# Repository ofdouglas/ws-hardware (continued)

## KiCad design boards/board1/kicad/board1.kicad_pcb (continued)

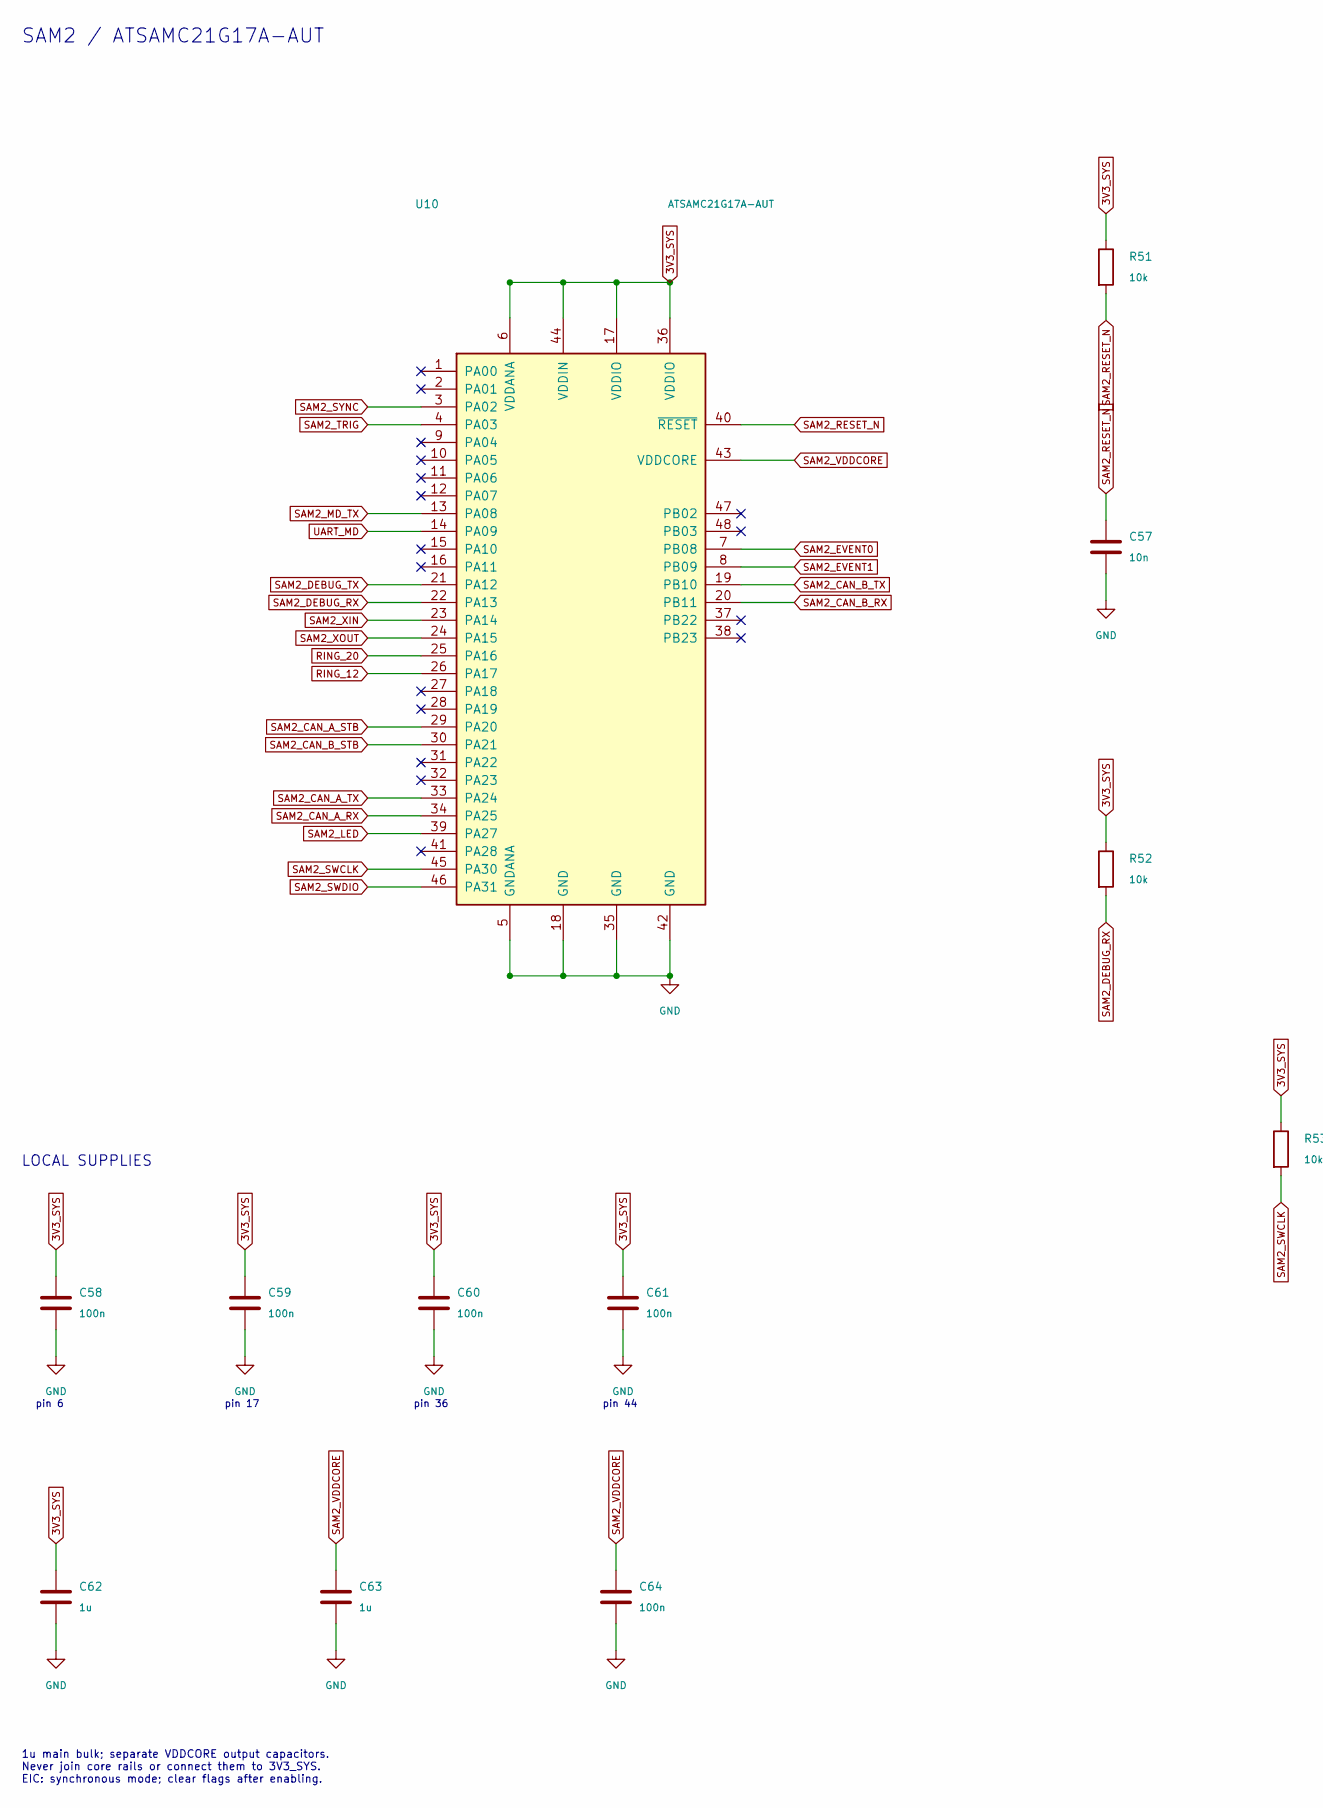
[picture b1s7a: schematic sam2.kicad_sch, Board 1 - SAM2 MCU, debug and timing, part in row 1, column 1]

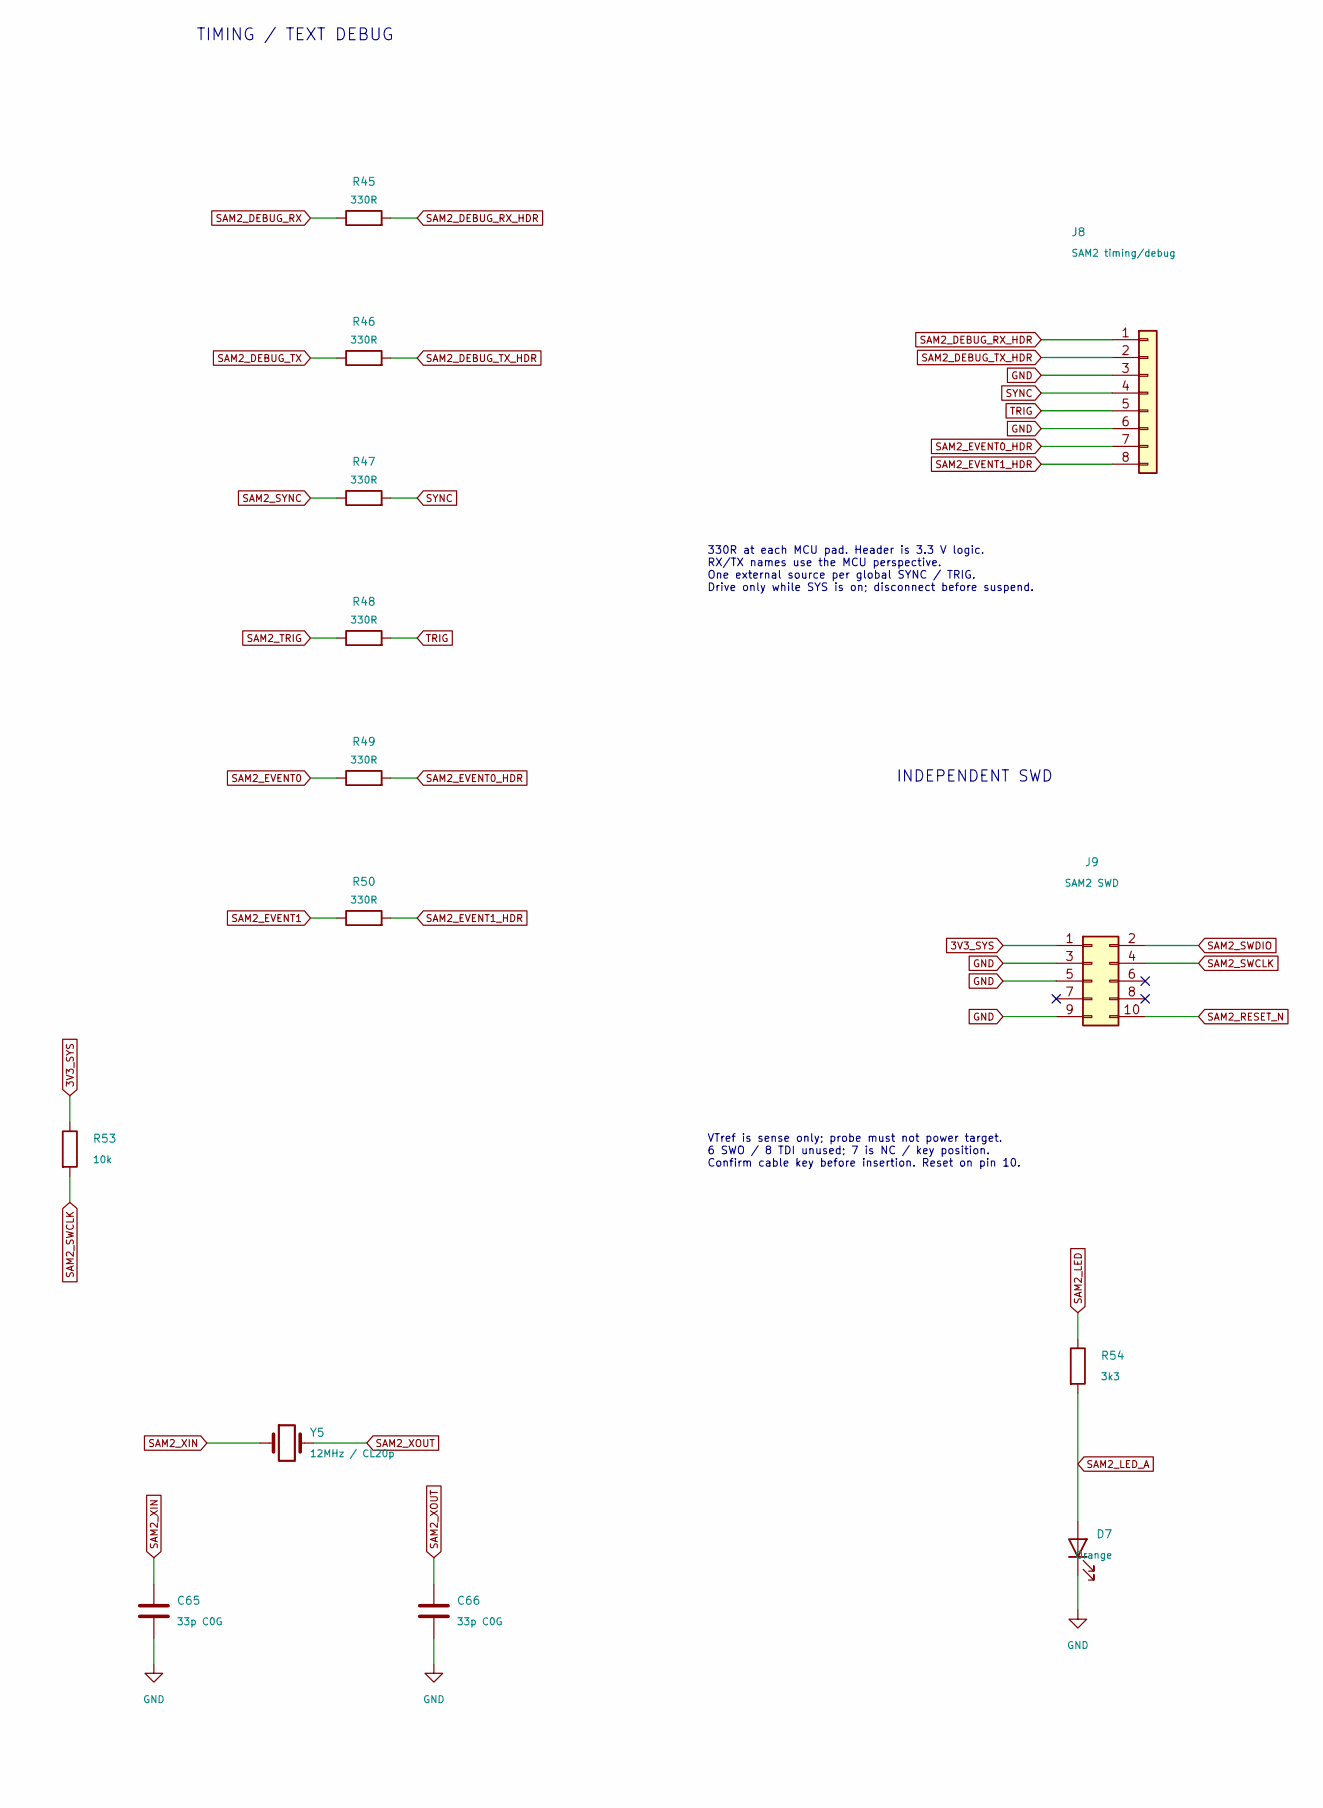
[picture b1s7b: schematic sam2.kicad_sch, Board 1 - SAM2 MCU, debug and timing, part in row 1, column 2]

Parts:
C57: 10n; C_0805_2012Metric; MPN CL21B103KBANNNC
C58, C59, C60, C61, C64: 100n; C_0805_2012Metric; MPN KGM21NR71E104KT
C62, C63: 1u; C_0805_2012Metric; MPN CL21B105KAFNFNE
C65, C66: 33p C0G; C_0805_2012Metric; MPN CC0805FRNPO9BN330
D7: Orange; LED_0603_1608Metric; MPN CSL1901DW1
J8: SAM2 timing/debug; PinHeader_1x08_P2.54mm_Vertical; MPN PRPC040SAAN-RC
J9: SAM2 SWD; CNC_Tech_3220-10-0100-00_2x05_P1.27mm_Vertical; MPN 3220-10-0100-00
R45, R46, R47, R48, R49, R50: 330R; R_0805_2012Metric; MPN CRGP0805F330R
R51, R52, R53: 10k; R_0805_2012Metric; MPN RMCF0805FT10K0
R54: 3k3; R_0805_2012Metric; MPN RK73H2ATTD3301F
U10: ATSAMC21G17A-AUT; TQFP-48_7x7mm_P0.5mm; MPN ATSAMC21G17A-AUT
Y5: 12MHz / CL20p; Crystal_SMD_ECS_CSM3X-2Pin_7.6x4.1mm; MPN ECS-120-20-3X-EN-TR

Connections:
3V3_SYS: C58.1, C59.1, C60.1, C61.1, C62.1, J9.1, R51.1, R52.1, R53.1, U10.6 (VDDANA), U10.17 (VDDIO), U10.36 (VDDIO), U10.44 (VDDIN); also elsewhere on the board
GND: C57.2, C58.2, C59.2, C60.2, C61.2, C62.2, C63.2, C64.2, C65.2, C66.2, D7.1 (K), J8.3, J8.6, J9.3, J9.5, J9.9, U10.5 (GNDANA), U10.18 (GND), U10.35 (GND), U10.42 (GND); also elsewhere on the board
RING_12: U10.26 (PA17); also elsewhere on the board
RING_20: U10.25 (PA16); also elsewhere on the board
SAM2_CAN_A_RX: U10.34 (PA25); also elsewhere on the board
SAM2_CAN_A_STB: U10.29 (PA20); also elsewhere on the board
SAM2_CAN_A_TX: U10.33 (PA24); also elsewhere on the board
SAM2_CAN_B_RX: U10.20 (PB11); also elsewhere on the board
SAM2_CAN_B_STB: U10.30 (PA21); also elsewhere on the board
SAM2_CAN_B_TX: U10.19 (PB10); also elsewhere on the board
SAM2_DEBUG_RX: R45.1, R52.2, U10.22 (PA13)
SAM2_DEBUG_RX_HDR: J8.1, R45.2
SAM2_DEBUG_TX: R46.1, U10.21 (PA12)
SAM2_DEBUG_TX_HDR: J8.2, R46.2
SAM2_EVENT0: R49.1, U10.7 (PB08)
SAM2_EVENT0_HDR: J8.7, R49.2
SAM2_EVENT1: R50.1, U10.8 (PB09)
SAM2_EVENT1_HDR: J8.8, R50.2
SAM2_LED: R54.1, U10.39 (PA27)
SAM2_LED_A: D7.2 (A), R54.2
SAM2_MD_TX: U10.13 (PA08); also elsewhere on the board
SAM2_RESET_N: C57.1, J9.10, R51.2, U10.40 (~RESET); also elsewhere on the board
SAM2_SWCLK: J9.4, R53.2, U10.45 (PA30)
SAM2_SWDIO: J9.2, U10.46 (PA31)
SAM2_SYNC: R47.1, U10.3 (PA02)
SAM2_TRIG: R48.1, U10.4 (PA03)
SAM2_VDDCORE: C63.1, C64.1, U10.43 (VDDCORE); also elsewhere on the board
SAM2_XIN: C65.1, U10.23 (PA14), Y5.1
SAM2_XOUT: C66.1, U10.24 (PA15), Y5.2
SYNC: J8.4, R47.2; also elsewhere on the board
TRIG: J8.5, R48.2; also elsewhere on the board
UART_MD: U10.14 (PA09); also elsewhere on the board

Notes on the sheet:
SAM2 / ATSAMC21G17A-AUT
TIMING / TEXT DEBUG
INDEPENDENT SWD
330R at each MCU pad. Header is 3.3 V logic. RX/TX names use the MCU perspective. One external source per global SYNC / TRIG. Drive only while SYS is on; disconnect before suspend.
VTref is sense only; probe must not power target. 6 SWO / 8 TDI unused; 7 is NC / key position. Confirm cable key before insertion. Reset on pin 10.
LOCAL SUPPLIES
pin 6
pin 17
pin 36
pin 44
1u main bulk; separate VDDCORE output capacitors. Never join core rails or connect them to 3V3_SYS. EIC: synchronous mode; clear flags after enabling.

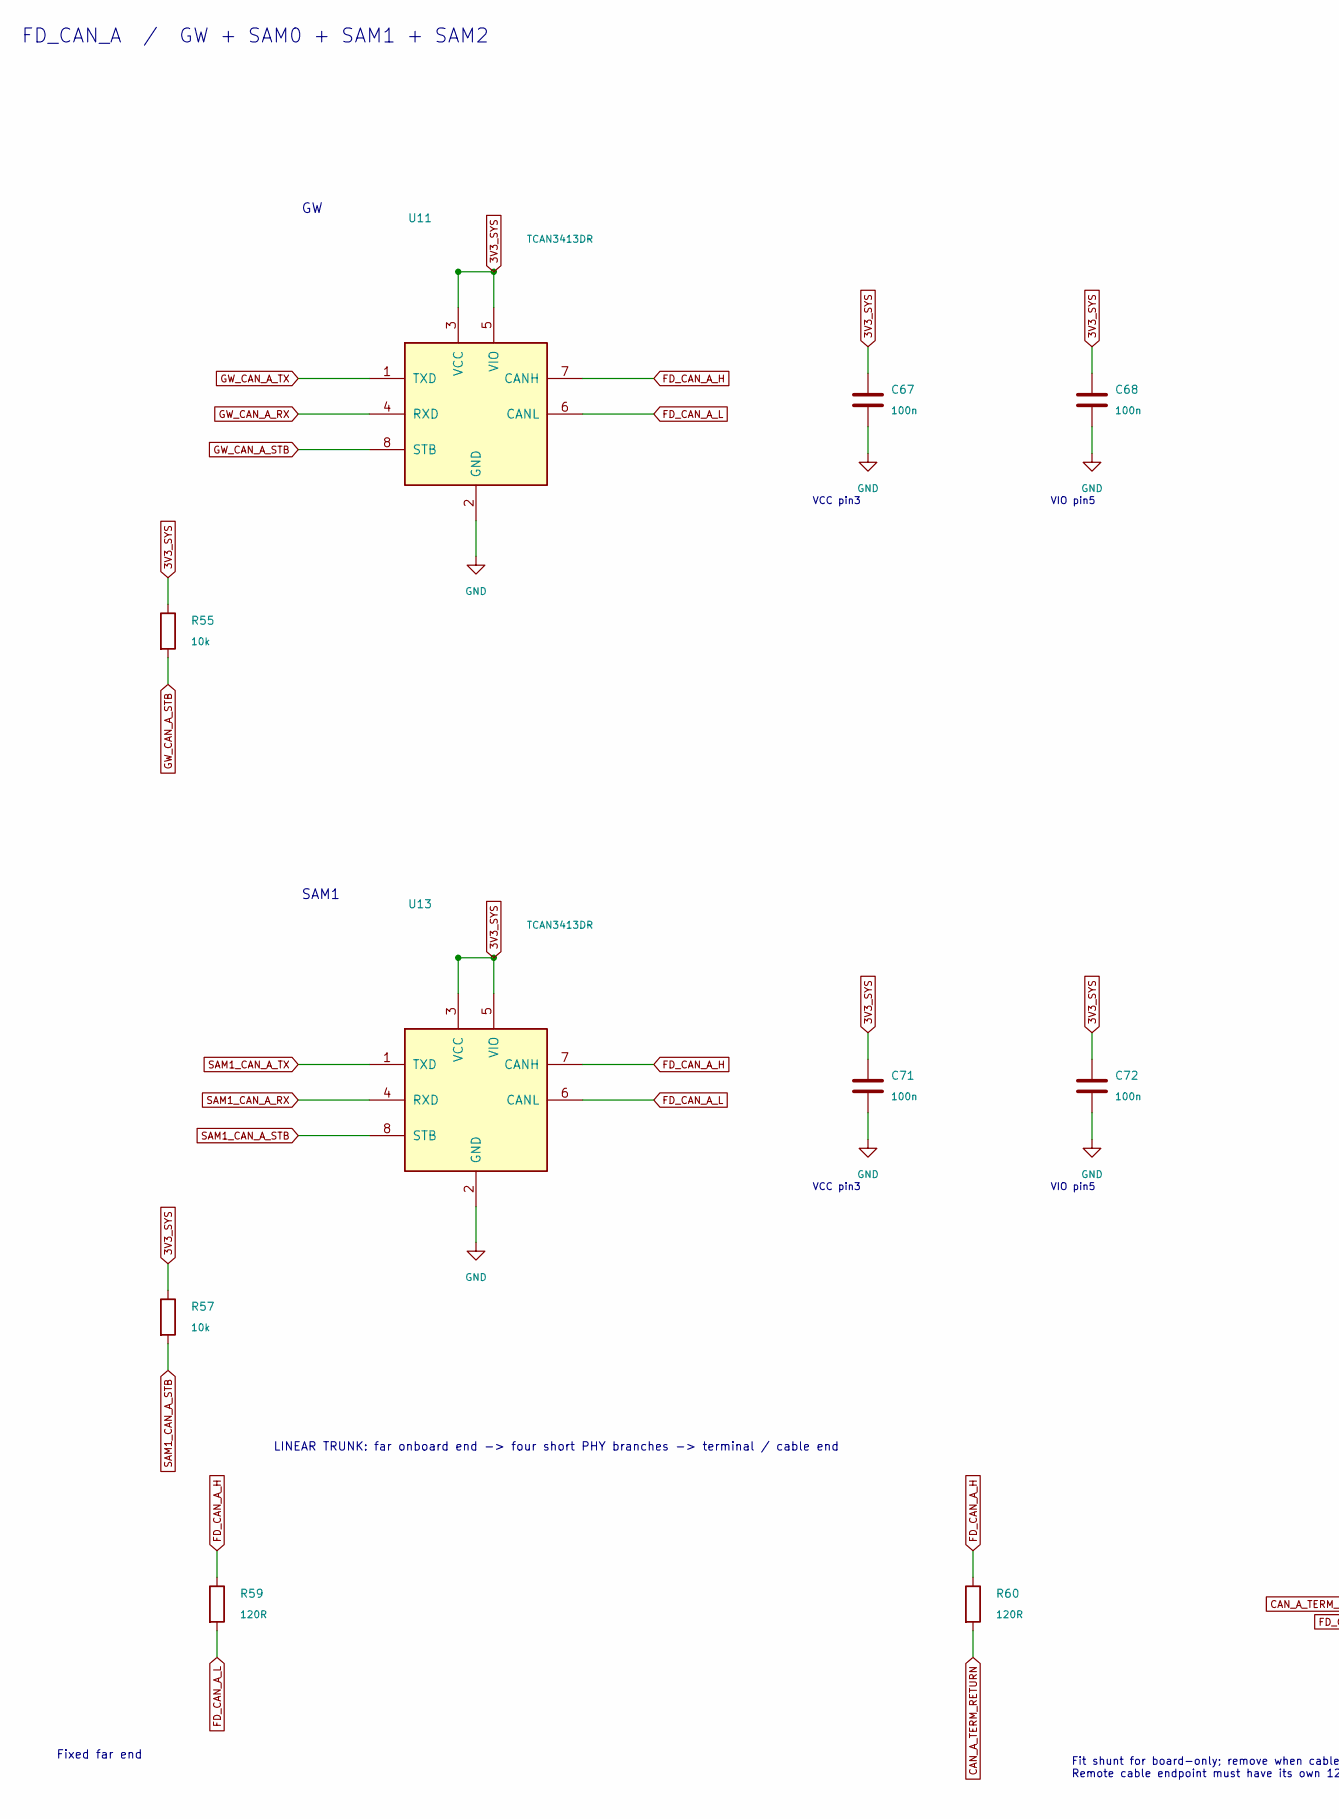
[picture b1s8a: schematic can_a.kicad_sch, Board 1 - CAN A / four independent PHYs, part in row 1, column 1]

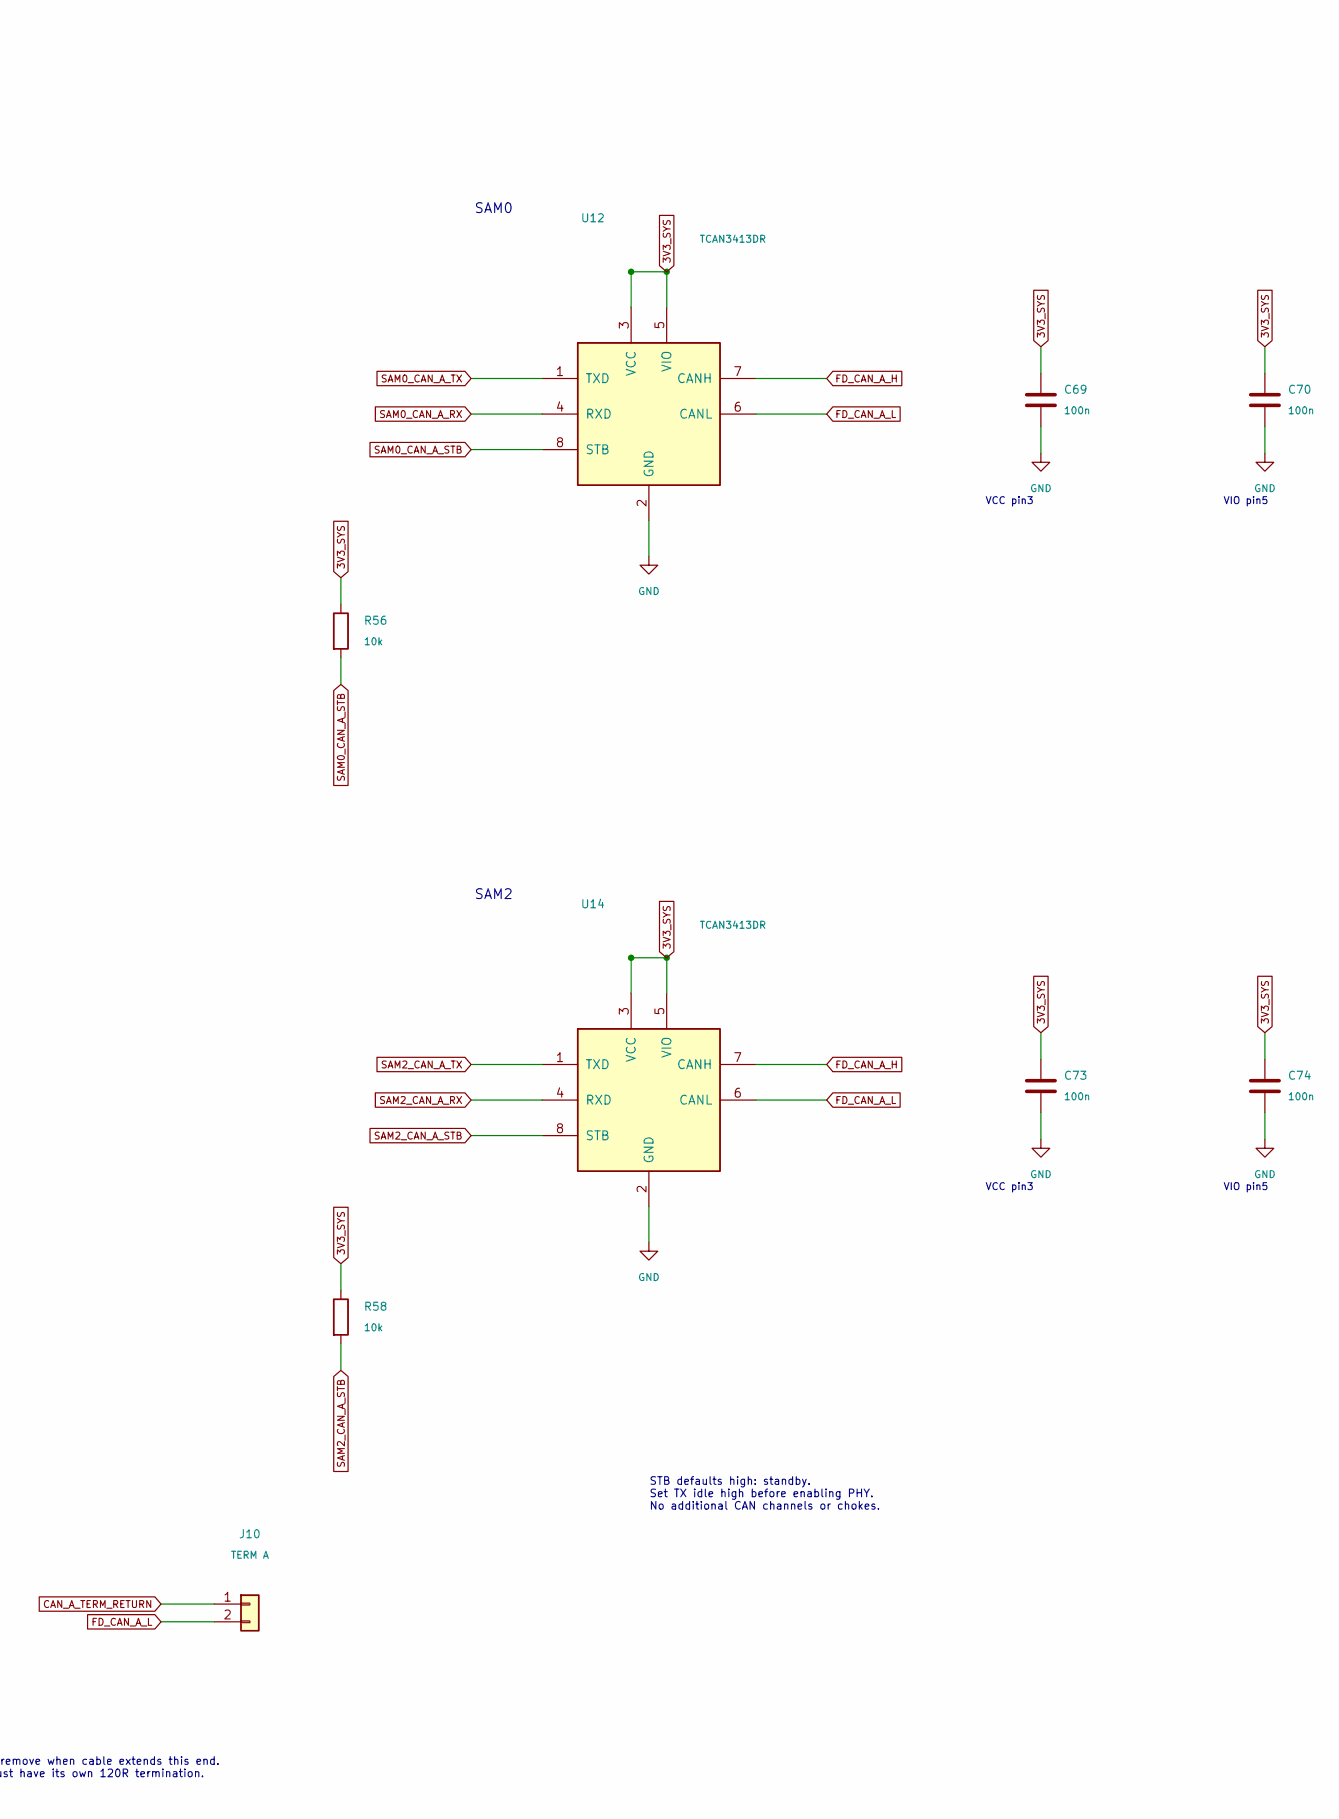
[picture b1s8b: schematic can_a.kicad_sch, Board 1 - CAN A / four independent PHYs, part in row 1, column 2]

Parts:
C67, C68, C69, C70, C71, C72, C73, C74: 100n; C_0805_2012Metric; MPN KGM21NR71E104KT
J10: TERM A; PinHeader_1x02_P2.54mm_Vertical; MPN PRPC002SAAN-RC
R55, R56, R57, R58: 10k; R_0805_2012Metric; MPN RMCF0805FT10K0
R59, R60: 120R; R_0805_2012Metric; MPN CRGP0805F120R
U11, U12, U13, U14: TCAN3413DR; SOIC-8_3.9x4.9mm_P1.27mm; MPN TCAN3413DR

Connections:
3V3_SYS: C67.1, C68.1, C69.1, C70.1, C71.1, C72.1, C73.1, C74.1, R55.1, R56.1, R57.1, R58.1, U11.3 (VCC), U11.5 (VIO), U12.3 (VCC), U12.5 (VIO), U13.3 (VCC), U13.5 (VIO), U14.3 (VCC), U14.5 (VIO); also elsewhere on the board
CAN_A_TERM_RETURN: J10.1, R60.2
FD_CAN_A_H: R59.1, R60.1, U11.7 (CANH), U12.7 (CANH), U13.7 (CANH), U14.7 (CANH); also elsewhere on the board
FD_CAN_A_L: J10.2, R59.2, U11.6 (CANL), U12.6 (CANL), U13.6 (CANL), U14.6 (CANL); also elsewhere on the board
GND: C67.2, C68.2, C69.2, C70.2, C71.2, C72.2, C73.2, C74.2, U11.2 (GND), U12.2 (GND), U13.2 (GND), U14.2 (GND); also elsewhere on the board
GW_CAN_A_RX: U11.4 (RXD); also elsewhere on the board
GW_CAN_A_STB: R55.2, U11.8 (STB); also elsewhere on the board
GW_CAN_A_TX: U11.1 (TXD); also elsewhere on the board
SAM0_CAN_A_RX: U12.4 (RXD); also elsewhere on the board
SAM0_CAN_A_STB: R56.2, U12.8 (STB); also elsewhere on the board
SAM0_CAN_A_TX: U12.1 (TXD); also elsewhere on the board
SAM1_CAN_A_RX: U13.4 (RXD); also elsewhere on the board
SAM1_CAN_A_STB: R57.2, U13.8 (STB); also elsewhere on the board
SAM1_CAN_A_TX: U13.1 (TXD); also elsewhere on the board
SAM2_CAN_A_RX: U14.4 (RXD); also elsewhere on the board
SAM2_CAN_A_STB: R58.2, U14.8 (STB); also elsewhere on the board
SAM2_CAN_A_TX: U14.1 (TXD); also elsewhere on the board

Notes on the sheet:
FD_CAN_A / GW + SAM0 + SAM1 + SAM2
VCC pin3
VIO pin5
SAM0
SAM1
SAM2
LINEAR TRUNK: far onboard end -> four short PHY branches -> terminal / cable end
Fixed far end
Fit shunt for board-only; remove when cable extends this end. Remote cable endpoint must have its own 120R termination.
STB defaults high: standby. Set TX idle high before enabling PHY. No additional CAN channels or chokes.

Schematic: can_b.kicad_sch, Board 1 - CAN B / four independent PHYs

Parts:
C75, C76, C77, C78, C79, C80, C81, C82: 100n; C_0805_2012Metric; MPN KGM21NR71E104KT
J11: TERM B; PinHeader_1x02_P2.54mm_Vertical; MPN PRPC002SAAN-RC
R61, R62, R63, R64: 10k; R_0805_2012Metric; MPN RMCF0805FT10K0
R65, R66: 120R; R_0805_2012Metric; MPN CRGP0805F120R
U15, U16, U17, U18: TCAN3413DR; SOIC-8_3.9x4.9mm_P1.27mm; MPN TCAN3413DR

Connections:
3V3_SYS: C75.1, C76.1, C77.1, C78.1, C79.1, C80.1, C81.1, C82.1, R61.1, R62.1, R63.1, R64.1, U15.3 (VCC), U15.5 (VIO), U16.3 (VCC), U16.5 (VIO), U17.3 (VCC), U17.5 (VIO), U18.3 (VCC), U18.5 (VIO); also elsewhere on the board
CAN_B_TERM_RETURN: J11.1, R66.2
FD_CAN_B_H: R65.1, R66.1, U15.7 (CANH), U16.7 (CANH), U17.7 (CANH), U18.7 (CANH); also elsewhere on the board
FD_CAN_B_L: J11.2, R65.2, U15.6 (CANL), U16.6 (CANL), U17.6 (CANL), U18.6 (CANL); also elsewhere on the board
GND: C75.2, C76.2, C77.2, C78.2, C79.2, C80.2, C81.2, C82.2, U15.2 (GND), U16.2 (GND), U17.2 (GND), U18.2 (GND); also elsewhere on the board
GW_CAN_B_RX: U15.4 (RXD); also elsewhere on the board
GW_CAN_B_STB: R61.2, U15.8 (STB); also elsewhere on the board
GW_CAN_B_TX: U15.1 (TXD); also elsewhere on the board
SAM0_CAN_B_RX: U16.4 (RXD); also elsewhere on the board
SAM0_CAN_B_STB: R62.2, U16.8 (STB); also elsewhere on the board
SAM0_CAN_B_TX: U16.1 (TXD); also elsewhere on the board
SAM1_CAN_B_RX: U17.4 (RXD); also elsewhere on the board
SAM1_CAN_B_STB: R63.2, U17.8 (STB); also elsewhere on the board
SAM1_CAN_B_TX: U17.1 (TXD); also elsewhere on the board
SAM2_CAN_B_RX: U18.4 (RXD); also elsewhere on the board
SAM2_CAN_B_STB: R64.2, U18.8 (STB); also elsewhere on the board
SAM2_CAN_B_TX: U18.1 (TXD); also elsewhere on the board

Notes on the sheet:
FD_CAN_B / GW + SAM0 + SAM1 + SAM2
VCC pin3
VIO pin5
SAM0
SAM1
SAM2
LINEAR TRUNK: far onboard end -> four short PHY branches -> terminal / cable end
Fixed far end
Fit shunt for board-only; remove when cable extends this end. Remote cable endpoint must have its own 120R termination.
STB defaults high: standby. Set TX idle high before enabling PHY. No additional CAN channels or chokes.

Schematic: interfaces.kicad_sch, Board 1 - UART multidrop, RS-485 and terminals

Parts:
C83, C84: 100n; C_0805_2012Metric; MPN KGM21NR71E104KT
R67, R68, R69, R70, R72, R73, R74, R75, R76, R77: 10k; R_0805_2012Metric; MPN RMCF0805FT10K0
R71: 470R; R_0805_2012Metric; MPN RMCF0805FT470R
R78, R80: 330R; R_0805_2012Metric; MPN CRGP0805F330R
R79: 120R; R_0805_2012Metric; MPN CRGP0805F120R
U19: SN74LV125APWR; TSSOP-14_4.4x5mm_P0.65mm; MPN SN74LV125APWR
U20: ST3485EBDR; SOIC-8_3.9x4.9mm_P1.27mm; MPN ST3485EBDR

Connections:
3V3_SYS: C83.1, C84.1, R67.1, R68.1, R69.1, R70.1, R71.1, R75.1, R76.1, R77.1, R78.1, U19.14 (VCC), U20.8 (VCC); also elsewhere on the board
GND: C83.2, C84.2, R72.2, R73.2, R74.2, R80.2, U19.2 (1A), U19.5 (2A), U19.7 (GND), U19.9 (3A), U19.12 (4A), U20.5 (GND); also elsewhere on the board
GW_MD_TX: R67.2, U19.1 (~1OE); also elsewhere on the board
GW_RS485_DE: R74.1, U20.3 (DE); also elsewhere on the board
GW_RS485_RE_N: R75.2, U20.2 (~RE); also elsewhere on the board
GW_RS485_RX: R77.2, U20.1 (RO); also elsewhere on the board
GW_RS485_TX: R76.2, U20.4 (DI); also elsewhere on the board
RS485_A: R78.2, R79.1, U20.6 (A); also elsewhere on the board
RS485_B: R79.2, R80.1, U20.7 (B); also elsewhere on the board
SAM0_MD_TX: R68.2, U19.4 (~2OE); also elsewhere on the board
SAM1_MD_TX: R69.2, U19.10 (~3OE); also elsewhere on the board
SAM2_MD_TX: R70.2, U19.13 (~4OE); also elsewhere on the board
SYNC: R72.1; also elsewhere on the board
TRIG: R73.1; also elsewhere on the board
UART_MD: R71.2, U19.3 (1Y), U19.6 (2Y), U19.8 (3Y), U19.11 (4Y); also elsewhere on the board

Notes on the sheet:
ONBOARD OPEN-DRAIN UART
All four RX inputs observe UART_MD. TX high releases; TX low sinks. No active-high drivers. Rate depends on measured rise time; firmware arbitrates.
EXTERNAL RS-485
DE low / RE_N high: reset shutdown. Fixed local termination; remote end also needs 120R. Both wires within +/-5.5 V of board GND (ADR-038).
Manual bench: disable / disconnect the RS-485 peer before USB power-off or suspend; bias can feed SYS. No automatic isolation or bias switch fitted.
Terminal block and TVS are on the test-access sheet.

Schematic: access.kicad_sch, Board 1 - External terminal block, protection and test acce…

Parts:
D8, D9: ESD2CAN24DBZRQ1; SOT-23; MPN ESD2CAN24DBZRQ1
D10: ESDS452DBZR; SOT-23; MPN ESDS452DBZR
J12: 1989803 / bus terminals; PhoenixContact_PTSA_0.5_8-2.5-F_1989803; MPN 1989803
J13: GW GND; PinHeader_1x02_P2.54mm_Vertical; MPN PRPC002SAAN-RC
J14: SAM0 GND; PinHeader_1x02_P2.54mm_Vertical; MPN PRPC002SAAN-RC
J15: SAM1 GND; PinHeader_1x02_P2.54mm_Vertical; MPN PRPC002SAAN-RC
J16: SAM2 GND; PinHeader_1x02_P2.54mm_Vertical; MPN PRPC002SAAN-RC
J17: POWER GND; PinHeader_1x02_P2.54mm_Vertical; MPN PRPC002SAAN-RC
J18: BUS GND; PinHeader_1x02_P2.54mm_Vertical; MPN PRPC002SAAN-RC
J19: CAN A; PinHeader_1x02_P2.54mm_Vertical; MPN PRPC002SAAN-RC
J20: CAN B; PinHeader_1x02_P2.54mm_Vertical; MPN PRPC002SAAN-RC
J21: RS485; PinHeader_1x02_P2.54mm_Vertical; MPN PRPC002SAAN-RC
J22: RING01; PinHeader_1x02_P2.54mm_Vertical; MPN PRPC002SAAN-RC
J23: RING12; PinHeader_1x02_P2.54mm_Vertical; MPN PRPC002SAAN-RC
J24: RING20; PinHeader_1x02_P2.54mm_Vertical; MPN PRPC002SAAN-RC
J25: UART_MD; PinHeader_1x02_P2.54mm_Vertical; MPN PRPC002SAAN-RC
TP1: VBUS_RAW; TestPoint_Pad_D2.0mm; MPN NA
TP2: USB_5V; TestPoint_Pad_D2.0mm; MPN NA
TP3: FTDI_3V3; TestPoint_Pad_D2.0mm; MPN NA
TP4: 3V3_SYS; TestPoint_Pad_D2.0mm; MPN NA
TP5: GW_RESET_N; TestPoint_Pad_D2.0mm; MPN NA
TP6: GW_BOOT0; TestPoint_Pad_D2.0mm; MPN NA
TP7: SAM0_RESET_N; TestPoint_Pad_D2.0mm; MPN NA
TP8: SAM0_VDDCORE; TestPoint_Pad_D2.0mm; MPN NA
TP9: SAM1_RESET_N; TestPoint_Pad_D2.0mm; MPN NA
TP10: SAM1_VDDCORE; TestPoint_Pad_D2.0mm; MPN NA
TP11: SAM2_RESET_N; TestPoint_Pad_D2.0mm; MPN NA
TP12: SAM2_VDDCORE; TestPoint_Pad_D2.0mm; MPN NA

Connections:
3V3_SYS: TP4.1; also elsewhere on the board
FD_CAN_A_H: D8.1 (IO1), J12.1, J19.1; also elsewhere on the board
FD_CAN_A_L: D8.2 (IO2), J12.2, J19.2; also elsewhere on the board
FD_CAN_B_H: D9.1 (IO1), J12.4, J20.1; also elsewhere on the board
FD_CAN_B_L: D9.2 (IO2), J12.5, J20.2; also elsewhere on the board
FTDI_3V3: TP3.1; also elsewhere on the board
GND: D8.3 (GND), D9.3 (GND), D10.3 (GND), J12.3, J12.8, J13.1, J13.2, J14.1, J14.2, J15.1, J15.2, J16.1, J16.2, J17.1, J17.2, J18.1, J18.2, J22.2, J23.2, J24.2, J25.2; also elsewhere on the board
GW_BOOT0: TP6.1; also elsewhere on the board
GW_RESET_N: TP5.1; also elsewhere on the board
RING_01: J22.1; also elsewhere on the board
RING_12: J23.1; also elsewhere on the board
RING_20: J24.1; also elsewhere on the board
RS485_A: D10.1 (IO1), J12.6, J21.1; also elsewhere on the board
RS485_B: D10.2 (IO2), J12.7, J21.2; also elsewhere on the board
SAM0_RESET_N: TP7.1; also elsewhere on the board
SAM0_VDDCORE: TP8.1; also elsewhere on the board
SAM1_RESET_N: TP9.1; also elsewhere on the board
SAM1_VDDCORE: TP10.1; also elsewhere on the board
SAM2_RESET_N: TP11.1; also elsewhere on the board
SAM2_VDDCORE: TP12.1; also elsewhere on the board
UART_MD: J25.1; also elsewhere on the board
USB_5V: TP2.1; also elsewhere on the board
VBUS_RAW: TP1.1; also elsewhere on the board

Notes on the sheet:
EXTERNAL BUS TERMINALS
TVS channels stay connected when CAN termination shunts are removed. Place all three arrays at terminal entry.
FITTED SCOPE GROUND POSTS
Six dedicated 1x2 headers, both contacts grounded. Place near the named circuit with room for a scope clip.
PCB TEST PADS — power / reset / core rails (TP1–TP12)

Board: 2 copper layers, 243 parts (0 on the bottom side), 152 nets, no tracks yet.

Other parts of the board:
H1, H2, H3, H4: M3 NPTH; MountingHole_3.2mm_M3

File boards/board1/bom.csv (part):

item_id,references,quantity,function,manufacturer,mpn,package,value,assembly,selection_status,evidence_status,symbol,footprint,requirements,adr,datasheet_evidence,sourcing_evidence,notes
B1-B001,U7,1,Gateway MCU,STMicroelectronics,STM32G474RBT6,LQFP64 (source; verify),NA,fit,accepted,unverified,MCU_ST_STM32G4:STM32G474RBTx,Package_QFP:LQFP-64_10x10mm_P0.5mm,B1-R001,ADR-004,DS12288 Rev.6 Fig.7 p.50; Tables12/13 pp.57-75; draft STM32 sheet linked in pinmap.md; ES0430 Rev.9 implementation review pending B1-Q005,TBD,Selected USR-15 / ADR-004; exact-device implementation and sourcing verification pending
B1-B002,U8; U9; U10,3,Leaf MCU,Microchip,ATSAMC21G17A-AUT,TQFP48 (source; verify),NA,fit,accepted,unverified,ATSAMC21G17A-AUT:ATSAMC21G17A-AUT,Package_QFP:TQFP-48_7x7mm_P0.5mm,B1-R001,ADR-004,DS60001479J sec.4.2.1 p.22; Table 6-2 pp.29-30; draft spreadsheet linked from pinmap.md; errata/footprint/electrical qualification pending B1-Q005; ../../libraries/symbols/ATSAMC21G17A-AUT/README.md (symbol evidence only; allocation remains unverified),TBD,Selected USR-15 / ADR-004; exact-device implementation and sourcing verification pending
B1-B003,U11; U12; U13; U14; U15; U16; U17; U18,8,CAN-FD PHYs,Texas Instruments,TCAN3413DR,SOIC-8; footprint review pending,TBD,fit,accepted,unverified,TCAN3413DR:TCAN3413DR,Package_SO:SOIC-8_3.9x4.9mm_P1.27mm,B1-R002,ADR-002,usb_input.md; TI SLLSFS8A; ../../libraries/symbols/TCAN3413DR/README.md (symbol pin evidence; board allocation unverified),2026-09-06 TI active; distributor stock/price TBD,TCAN3413DR selected USR-06; eight Rev A; ninth only in expanded Board 1; implementation unverified
B1-B004,U4,1,USB-UART bridge,FTDI,FT232HL-REEL,LQFP48; footprint review pending,TBD,fit,accepted,unverified,Board1:FT232HL_BusPowered,Package_QFP:LQFP-48_7x7mm_P0.5mm,B1-R005,ADR-001,FT232H DS_FT232H v2.2 pp.6-10 and Fig.6.1 p.45; kicad/README.md; full current errata/inventory reconciliation pending,USR-03: FT232HL on hand; linked ordering code 768-1101-1-ND,Captured U4 with project-local bus-powered symbol correcting VCCD/EECLK/EECS electrical types; pin numbers unchanged. On hand per user; exact inventory suffix/silicon revision to reconcile. Workbook B1-P233-280 remains unverified; see pinmap.md for CAD naming mapping.
B1-B005,J1,1,USB 2.0 Standard-B receptacle,On Shore Technology Inc.,USB-B1HSB6,TBD,TBD,fit,accepted,unverified,Connector:USB_B,Connector_USB:USB_B_OST_USB-B1HSxx_Horizontal,B1-R005,ADR-001; ADR-030,TBD,DigiKey ED2983-ND; https://www.digikey.com/en/products/detail/on-shore-technolo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,"J1 pins 1 VBUS, 2 DM, 3 DP, 4 GND, 5 shell. Draft connects shell directly to ground at entry. KiCad OST USB-B1HSxx footprint selected; exact housing/drill/land-pattern approval before layout remains B1-Q004."
B1-B006,D1,1,VBUS TVS,Littelfuse,SMF6.0A,SOD-123F,TBD,fit,accepted,unverified,Device:D,Diode_SMD:D_SOD-123F,B1-R006,ADR-019; ADR-022; ADR-024,usb_input.md,TBD,ESD/hotplug only; not a guaranteed <=6 V clamp or polarity/OVP circuit Captured in KiCad power/USB section; see kicad/README.md. Evidence remains unverified pending schematic/footprint approval.
B1-B007,NA,0,Remaining CAN interface protection,TBD,TBD,TBD,TBD,tbd,proposed,unverified,TBD,TBD,B1-R009,ADR-002; ADR-034; ADR-037,termination.md; B1-Q003/004,TBD,Residual allocation fully enumerated in completed schematic; no unassigned components or DNP footprints. See complete capture notes.
B1-B008,R67; R68; R69; R70,4,UART_MD driver /OE pull-up resistors,Stackpole Electronics Inc.,RMCF0805FT10K0,0805,10 kohm +/-1%; 0.125 W,fit,accepted,unverified,Device:R,Resistor_SMD:R_0805_2012Metric,B1-R003,ADR-033; ADR-039,https://www.seielect.com/Catalog/SEI-RMCF_RMCP.pdf ; ADR-033; B1-Q003,RMCF0805FT10K0CT-ND; refresh before purchase,"USR-33 accepts multidrop plan. Four /OE pull-ups to 3V3_SYS, one per driver channel. Shared bus pull-up split to B1-B074; driver B1-B066 and bypass B1-B036 counted separately. Reset/ramp/timing and baud remain unverified."
B1-B009,J3; J5; J7; J9,4,Independent Cortex SWD/reset headers,CNC Tech,3220-10-0100-00,Through-hole; 2 x 5; 1.27 mm; shrouded keyed header; footprint TBD,10 positions,fit,accepted,unverified,Connector_Generic:Conn_02x05_Odd_Even,Board1:CNC_Tech_3220-10-0100-00_2x05_P1.27mm_Vertical,B1-R007,ADR-011; ADR-026 (026-reva-connectors.md),https://www.cnctech.us/pdfs/3220-XX-0100-00_.pdf ; p.1; revision and footprint review TBD B1-Q004,DigiKey 1175-1627-ND; https://www.digikey.com/en/products/detail/cnc-tech/3220-10-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 ; refresh stock/price before purchase,Exact MPN selected USR-25 / ADR-026; four independent MCU headers. All ten contacts supplied; review position-7 removal against actual cable. Adapter/probe support and USB-only target-power behavior pending B1-Q004/005. Manufacturer drawing matched to native footprint; see kicad/footprint_checks.md. Physical sample/mating checks remain before layout approval.
B1-B010,NA,0,Remaining MCU boot/reset support,TBD,TBD,TBD,TBD,tbd,proposed,unverified,TBD,TBD,B1-R001,ADR-004,TBD,TBD,Residual allocation fully enumerated in completed schematic; no unassigned components or DNP footprints. See complete capture notes.
B1-B011,TP1; TP2; TP3; TP4; TP5; TP6; TP7; TP8; TP9; TP10; TP11; TP12; TP13; TP14; TP15; TP16; TP17; TP18; TP19,0,PCB test pads; no purchased components,NA,NA,PCB copper pads,2 mm exposed copper test pad; 19 placements,tbd,accepted,unverified,Connector:TestPoint,TestPoint:TestPoint_Pad_D2.0mm,B1-R008,ADR-039,TBD,TBD,"Nineteen pads, zero purchased parts. Named signals in schematic. Layout must keep high-speed observation branches short."
B1-B012,U2,1,3.3 V buck regulator,Texas Instruments,TPS560430X3FDBVR,SOT-23-6,3.3 V fixed; 600 mA; 1.1 MHz FPWM,fit,accepted,unverified,TPS560430X3FDBVR:TPS560430X3FDBVR,Package_TO_SOT_SMD:SOT-23-6,B1-R006; B1-R012; B1-R023,ADR-021,https://www.ti.com/lit/ds/symlink/tps560430.pdf; ../../libraries/symbols/TPS560430X3FDBVR/README.md (symbol pin evidence; board allocation unverified),DigiKey 296-51994-1-ND,Explicit user selection ADR-021; replaces SC189. Filter MPNs accepted ADR-025; electrical filter/startup qualification remains open. Captured in KiCad power/USB section; see kicad/README.md. Evidence remains unverified pending schematic/footprint approval.
B1-B013,U5,1,FTDI configuration EEPROM,Microchip Technology,AT93C56B-SSHM-B,SOIC-8; 3.9 mm body; 1.27 mm pitch; footprint TBD,2 Kbit; 128 x 16; 3.3 V,fit,accepted,unverified,AT93C56B-SSHM-B:AT93C56B-SSHM-B,Package_SO:SOIC-8_3.9x4.9mm_P1.27mm,B1-R005; B1-R006; B1-R012,ADR-001; ADR-018,DS20006260B pp.3-9 and 31; FT_000288 v2.2 Table 3.3 and section 7; ADR-018; ../../libraries/symbols/AT93C56B-SSHM-B/README.md (symbol pin evidence; board allocation unverified),DigiKey AT93C56B-SSHM-B-ND; https://www.digikey.com/en/products/detail/microchip-technol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 ; quantity-one tube listing; refresh stock/price before purchase,Selected USR-23; ORG to VCC for x16; powered from FTDI VCCD. B1-P281-288 draft sheet. Clock/startup/word-program/footprint qualification B1-Q012; supports 1 MHz at 3.3 V. DO series resistor B1-B056; pull-up B1-B065; bypass B1-B061; residual support B1-B017. Captured in KiCad power/USB section; see kicad/README.md. Evidence remains unverified pending schematic/footprint approval.
B1-B014,Y1,1,FTDI crystal,ECS Inc.,ECS-120-18-5PX-CKM-TR,HC-49/US leaded SMT; 11.4 x 4.8 x 4.3 mm; footprint TBD,12 MHz; CL 18 pF,fit,accepted,unverified,Device:Crystal,Crystal:Crystal_SMD_HC49-SD,B1-R005; B1-R006; B1-R012,ADR-001; ADR-017; ADR-030,CSM-7X Rev.2020 p.1; 25 ppm first-year screen before loading; crystal_networks.md,DigiKey 50-ECS-120-18-5PX-CKM-CT-ND; 2026-09-06 browser stock 2149; qty1 USD 0.54; recheck before purchase,Exact ECS-120-18-5PX-CKM-TR finalized by user ADR-030. Loading/startup/drive and temperature/lifetime qualification remain B1-Q008. Captured in KiCad power/USB section; see kicad/README.md. Evidence remains unverified pending schematic/footprint approval.
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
